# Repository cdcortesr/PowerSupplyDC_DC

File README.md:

# PowerSupplyDC_DC
Vin=34V, Vout=12V Iout=2A nom.

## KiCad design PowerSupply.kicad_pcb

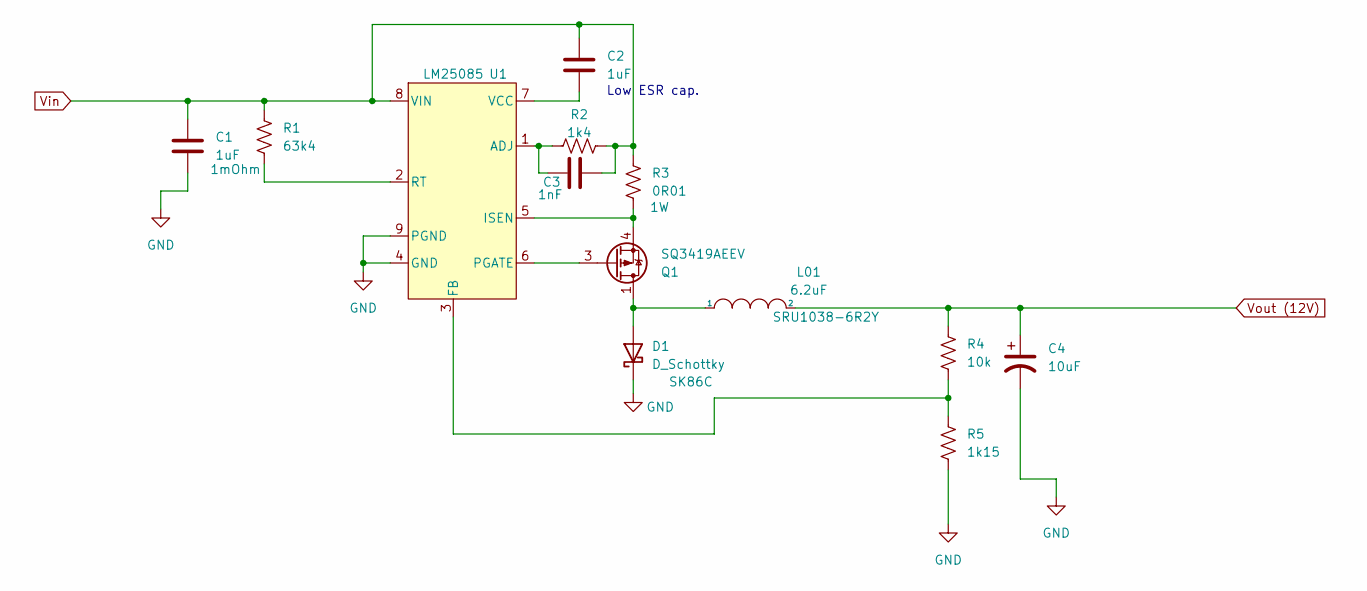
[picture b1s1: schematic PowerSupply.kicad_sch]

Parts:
C1: 1uF; C_1210_3225Metric_Pad1.33x2.70mm_HandSolder; MFR Part # CC1210KKX7R0BB105; LCSC Part # C577270
C2: 1uF; C_0402_1005Metric_Pad0.74x0.62mm_HandSolder; MFR Part # GRM155R61H105KE05D; LCSC Part # C1518208
C3: 1nF; C_0402_1005Metric_Pad0.74x0.62mm_HandSolder; MFR Part # GRM1555C1H102JA01D; LCSC Part # C76947
C4: 10uF; C_1206_3216Metric_Pad1.33x1.80mm_HandSolder; MFR Part # TCJA106M025R0150E; LCSC Part # C2158829
D1: D_Schottky; D_SMC; MFR Part # SK86C; LCSC Part # C64338
L01: 6.2uF; L_Bourns-SRU1028_10.0x10.0mm; MFR Part # SRU1038-6R2Y; LCSC Part # C7084591
Q1: SQ3419AEEV; TSOP-6_1.65x3.05mm_P0.95mm; MFR Part # LM25085MY/NOPB; LCSC Part # C2650243
R1: 63k4; R_0805_2012Metric_Pad1.20x1.40mm_HandSolder; MFR Part # FRC0805F6342TS; LCSC Part # C2933483
R2: 1k4; R_0805_2012Metric_Pad1.20x1.40mm_HandSolder; MFR Part # FRC0805F1401TS; LCSC Part # C2930161
R3: 0R01; R_1206_3216Metric_Pad1.30x1.75mm_HandSolder; MFR Part # HoJLR1206-1W-10mR-1%; LCSC Part # C2903499
R4: 10k; R_0805_2012Metric_Pad1.20x1.40mm_HandSolder; MFR Part # FRC0805J103TS; LCSC Part # C2930231
R5: 1k15; R_0805_2012Metric_Pad1.20x1.40mm_HandSolder; MFR Part # SCR0805F1K15; LCSC Part # C3016680
U1: LM25085; HVSSOP-8-1EP_3x3mm_P0.65mm_EP1.57x1.89mm_ThermalVias; MFR Part # SQ3419AEEV-T1_GE3; LCSC Part # C727535

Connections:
GND: C1.2, C4.2, D1.1 (K), R5.2, U1.4 (GND), U1.9 (PGND)
unnamed: D1.2 (A), L01.1, Q1.1 (D), Q1.2 (D), Q1.5 (D), Q1.6 (D)
unnamed: Q1.3 (G), U1.6 (PGATE)
unnamed: Q1.4 (S), R3.2, U1.5 (ISEN)
unnamed: C3.1, R2.1, U1.1 (ADJ)
unnamed: R4.2, R5.1, U1.3 (FB)
unnamed: R1.2, U1.2 (RT)
unnamed: C2.2, U1.7 (VCC)
Vin: C1.1, C2.1, C3.2, R1.1, R2.2, R3.1, U1.8 (VIN)
Vout (12V): C4.1, L01.2, R4.1

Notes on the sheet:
Low ESR cap.

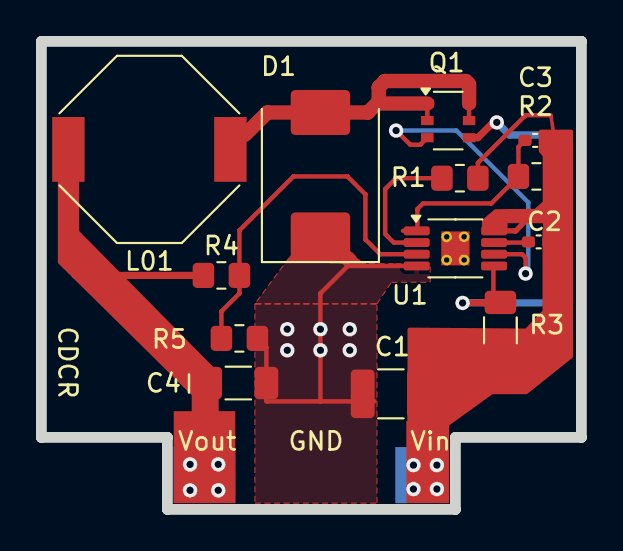
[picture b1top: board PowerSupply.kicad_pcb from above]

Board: 2 copper layers, 30.0 x 26.0 mm, 13 parts (0 on the bottom side), 10 nets.

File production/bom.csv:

Designator,Footprint,Quantity,Value,LCSC Part #
C1,1210,1,1uF,C577270 
C2,0402,1,1uF,C1518208 
C3,0402,1,1nF,C76947
C4,1206,1,10uF,C2158829
D1,D_SMC,1,D_Schottky,C64338
L01,L_Bourns-SRU1028_10.0x10.0mm,1,6.2uF,C7084591
Q1,TSOP-6_1.65x3.05mm_P0.95mm,1,SQ3419AEEV,C2650243
R1,0805,1,63k4,C2933483
R2,0805,1,1k4,C2930161
R3,1206,1,0R01,C2903499
R4,0805,1,10k,C2930231
R5,0805,1,1k15,C3016680
U1,HVSSOP-8-1EP_3x3mm_P0.65mm_EP1.57x1.89mm_ThermalVias,1,LM25085,C727535

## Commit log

2025-08-18 Initial upload
2025-08-18 Second commit
2025-08-19 update design file
2025-08-19 PMOS update
2025-08-21 Update Schm 08/21
2025-08-21 Sch update 08/21
2025-08-25 Update 08/24
2025-08-25 Update 08/25
2025-08-26 update 08-26
2025-08-27 update 08-27
2025-08-28 Update 27-08
2025-08-28 Update 08-28
2025-08-29 Update 08-29
2025-09-02 Final Layout
